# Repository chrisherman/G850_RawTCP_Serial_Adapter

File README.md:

**WiFi Raw-TCP Serial Adapter for the Sharp PC-G850** <br>
A Serial to TCP/IP adapter for the Sharp G850V(S) using the 11-pin port and an ESP8266<br>

**Initial Configuration**<br>
config.h contains all relevant default parameters.<br> 
The firmware looks for a config.ini file in LittleFS and will only use the firmware defaults if no config file can be loaded<br>
(note that if you initialize your ESL with SPIFFs, you can upload a config.ini file until your hair falls out - it will always be wiped when the software initializes LittleFS, so make sure you upload any configuration file using LittleFS filesystem)

**AT commands**  (can be set via netcat/telnet or via the G850, e.g. you could save the AT command in text editor and then "save" via the SIO port) to change the WiFI SSID and password or other parameters.<br>
**+++AT+CFG?**<br>
Returns: +++AT+CFG={"rev":1,"sleep":60,"baud":9600,"port":23,"ssid":"GUEST","wifipw":"your_pw_here","host":"G850V.local","otapw":"myOTAPW"}<br> 
The command displays the active configuration<br>

**+++AT+CFG={ "rev":\<n>,<br>
            "sleep":\<n>,<br>
            "baud":\<n>,<br>
            "port":\<n>,<br>
            "ssid":"GUEST",<br>
            "wifipw":"new_pw",<br>
            "host":"G850V.local",<br>
            "otapw":"myOTAPW"} <br>**
Returns: OK

Sets a new configuration. you can set just one parameter or all at once.<br>
**rev**: integer, referencing the version of the configuration. I recommend leaving at 1<br>
**sleep**: seconds until unit goes into deep sleep<br>
**baud**: baudrate for connection with G850 (600...9600)<br>
**port**: TCP/IP port (use 23 for telnet compatibility)<br>
**ssid**: the ssid name of your wifi<br>
**wifipw**: password of your wifi network<br>
**host**: hostname for use when requesting an IP address<br> 
**otapw**: password for protrcting your ota passwords (use espota protocol)<br>

Example:<br>
+++AT+CFG={"ssid":"GUEST","wifipw":"pw"}<br>

**+++AT+SAVE**<br>
Returns: OK
saves current configuration as failsafe.ini to LittleFS Flash file system.<br>
**Pressing the PRG button for longer than 5 sec will load failsafe.ini configuration and reboot.**
This allows you to recover from a messed-up config.ini (e.g. wrong wifi credentials)<br>

**+++AT+SLEEP**<BR>
Puts the adapter immediately into sleep.<br>
Returns: OK<br>

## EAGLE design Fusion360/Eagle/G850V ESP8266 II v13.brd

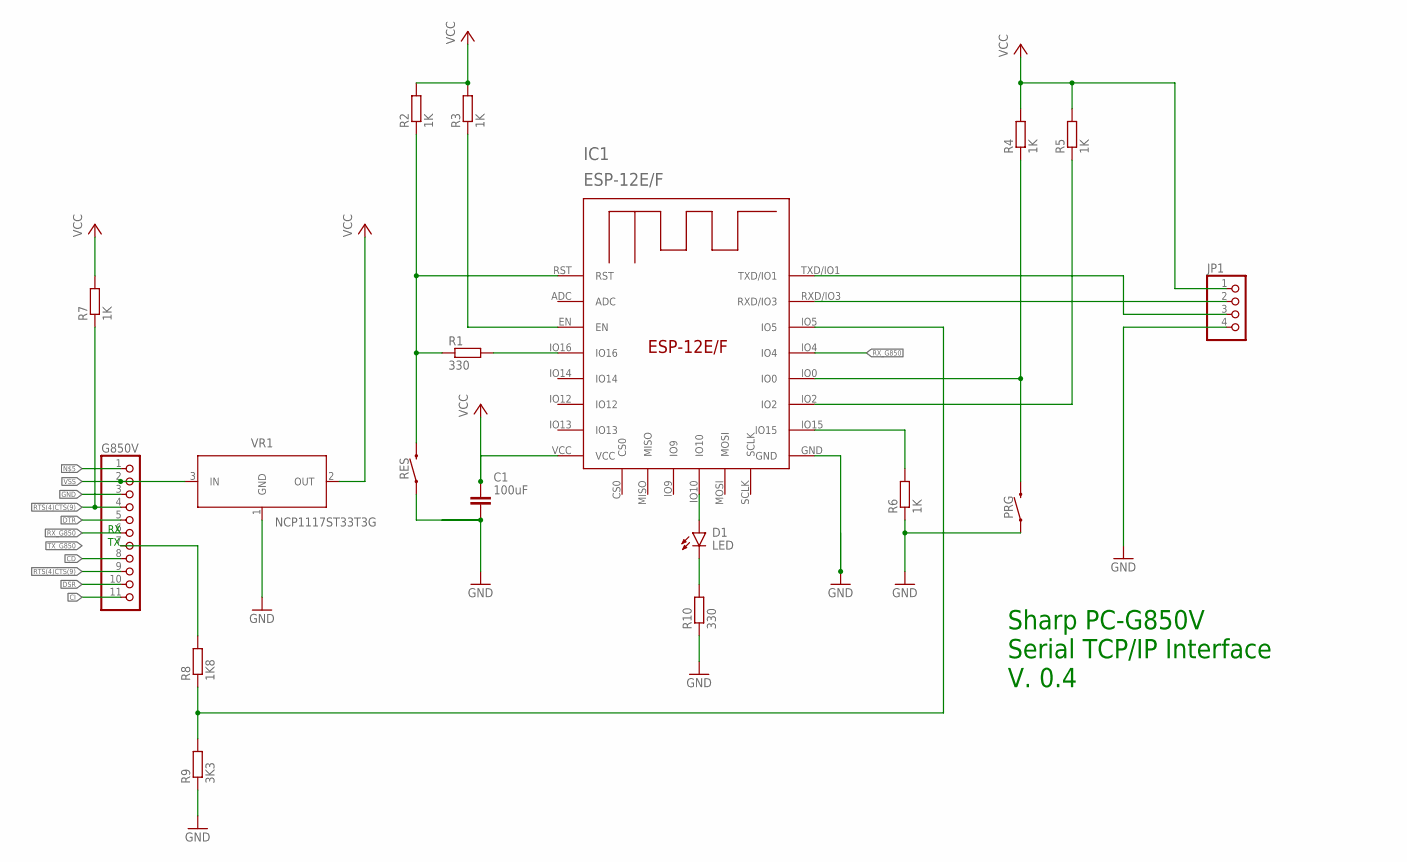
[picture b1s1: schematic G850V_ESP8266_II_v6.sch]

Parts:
C1: 100uF; CAPC4532X135
D1: LED; LEDC2012X110N_FLAT-B
G850V: PINHD-1X11/90; 1X11/90
IC1: ESP-12E/F; ESP-12E
JP1: PINHD-1X4/90; 1X04/90
PRG: MOMENTARY-SWITCH-SPST-SMD-4.6X2.8MM; TACTILE_SWITCH_SMD_4.6X2.8MM
R1, R10: 330; R0805
R2, R3, R4, R5, R6, R7: 1K; R0805
R8: 1K8; R0805
R9: 3K3; R0805
RES: MOMENTARY-SWITCH-SPST-SMD-4.6X2.8MM; TACTILE_SWITCH_SMD_4.6X2.8MM
VR1: NCP1117ST33T3G; SOT230P700X170-4

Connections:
CD: G850V.8
CI: G850V.11
DSR: G850V.10
DTR: G850V.5
GND: C1.2, G850V.3, IC1.GND, JP1.4, PRG.1, PRG.2 (1), R6.1, R9.1, R10.1, RES.1, RES.2 (1), VR1.1 (GND)
unnamed: IC1.RXD/IO3, JP1.2
unnamed: IC1.IO15, R6.2
unnamed: IC1.IO0, PRG.3 (2), PRG.4 (2), R4.1
unnamed: IC1.TXD/IO1, JP1.3
unnamed: IC1.IO2, R5.1
unnamed: IC1.IO16, R1.2
unnamed: IC1.RST, R1.1, R2.1, RES.3 (2), RES.4 (2)
unnamed: IC1.IO5, R8.1, R9.2
unnamed: IC1.EN, R3.1
unnamed: D1.A, IC1.IO10
unnamed: D1.C, R10.2
RTS(4)CTS(9): G850V.4, G850V.9, R7.1
RX_G850: G850V.6, IC1.IO4
TX_G850: G850V.7, R8.2
VCC: C1.1, IC1.VCC, JP1.1, R2.2, R3.2, R4.2, R5.2, R7.2, VR1.2 (OUT)
VSS: G850V.2, VR1.3 (IN)

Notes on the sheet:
Sharp PC-G850V Serial TCP/IP Interface V. 0.4

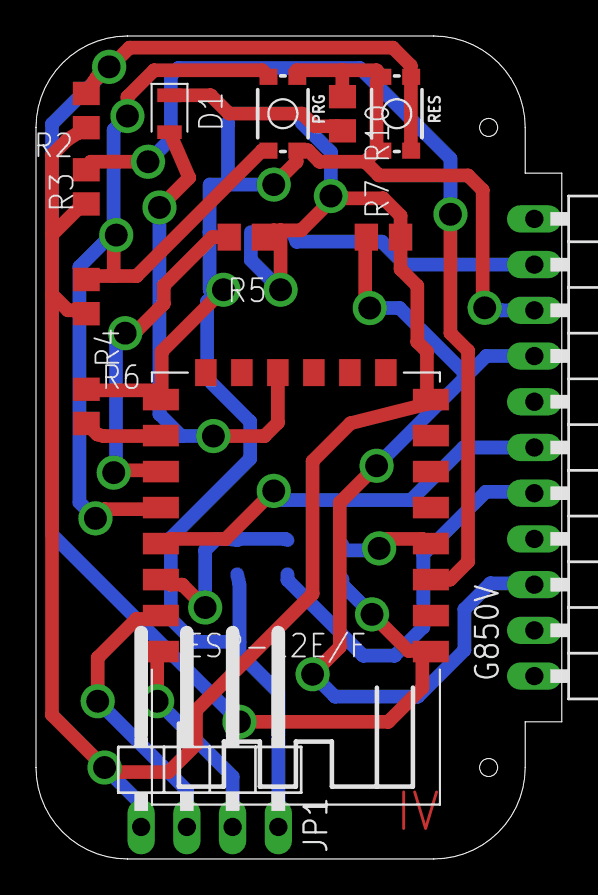
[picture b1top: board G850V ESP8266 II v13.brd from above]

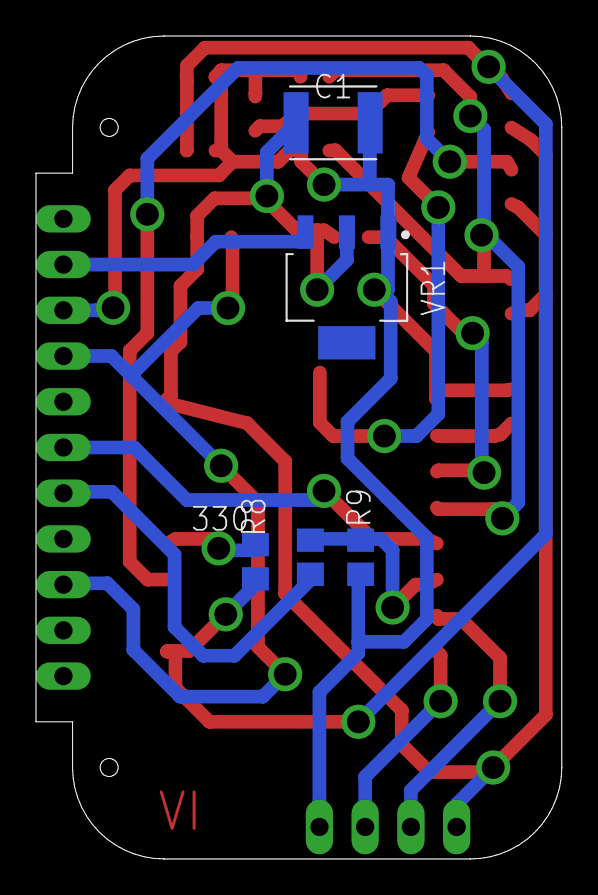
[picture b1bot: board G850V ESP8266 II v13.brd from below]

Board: 2 copper layers, 29.2 x 45.7 mm, 18 parts (5 on the bottom side), 17 nets.

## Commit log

2022-02-13 workable version
2022-02-13 updated formatting
2022-02-15 updated descriptions
2022-02-15 updated AT commands
2022-02-15 updated Fusion360 files and descriptions
2022-02-15 updated description
2022-02-15 updated desc
2022-02-28 replaced AT command parser to find AT commands not at beginning of a line

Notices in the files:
parts and their libraries:
SparkFun-Switches: Licensing: Creative Commons ShareAlike 4.0 International - https://creativecommons.org/licenses/by-sa/4.0
